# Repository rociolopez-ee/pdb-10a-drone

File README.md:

# 🔋 Drone Power Distribution Board

A 2-layer power distribution PCB designed for lightweight drones. Capable of distributing up to **10A of current**, this board is optimized for compact layouts and robust power handling.

## 📐 Board Specifications

- **Layers**: 2  
- **Board Size**: 2.0924 x 3.4843 in (5.31 x 8.85 cm)  
- **Max Current**: 10A  
- **Application**: Power regulation and distribution for quadcopters or fixed-wing drones  
- **Copper Weight**: 2 oz  
- **Input Voltage Range**: 7V–25V (3S–6S LiPo)

## 🛠️ Features

- Input via XT60 or direct-solder pads
- Multiple output rails (ESCs, accessories, BEC)
- Wide ground and V+ copper pours for high current
- Mounting holes for vibration-isolated installation
- Compatible with common LiPo packs and drone frames

## 📁 Repository Contents

- `/schematics/` – Schematic files (.kicad_sch)
- `/pcb_layout/` – PCB layout files (.kicad_pcb) + Gerbers
- `/BOM/` – Bill of Materials (CSV or Excel)
- `/images/` – Board renderings and layout previews

## 🖼️ Preview

## 👩‍💻 Designed by

[Rocio Lopez](https://github.com/rociolopez)

---

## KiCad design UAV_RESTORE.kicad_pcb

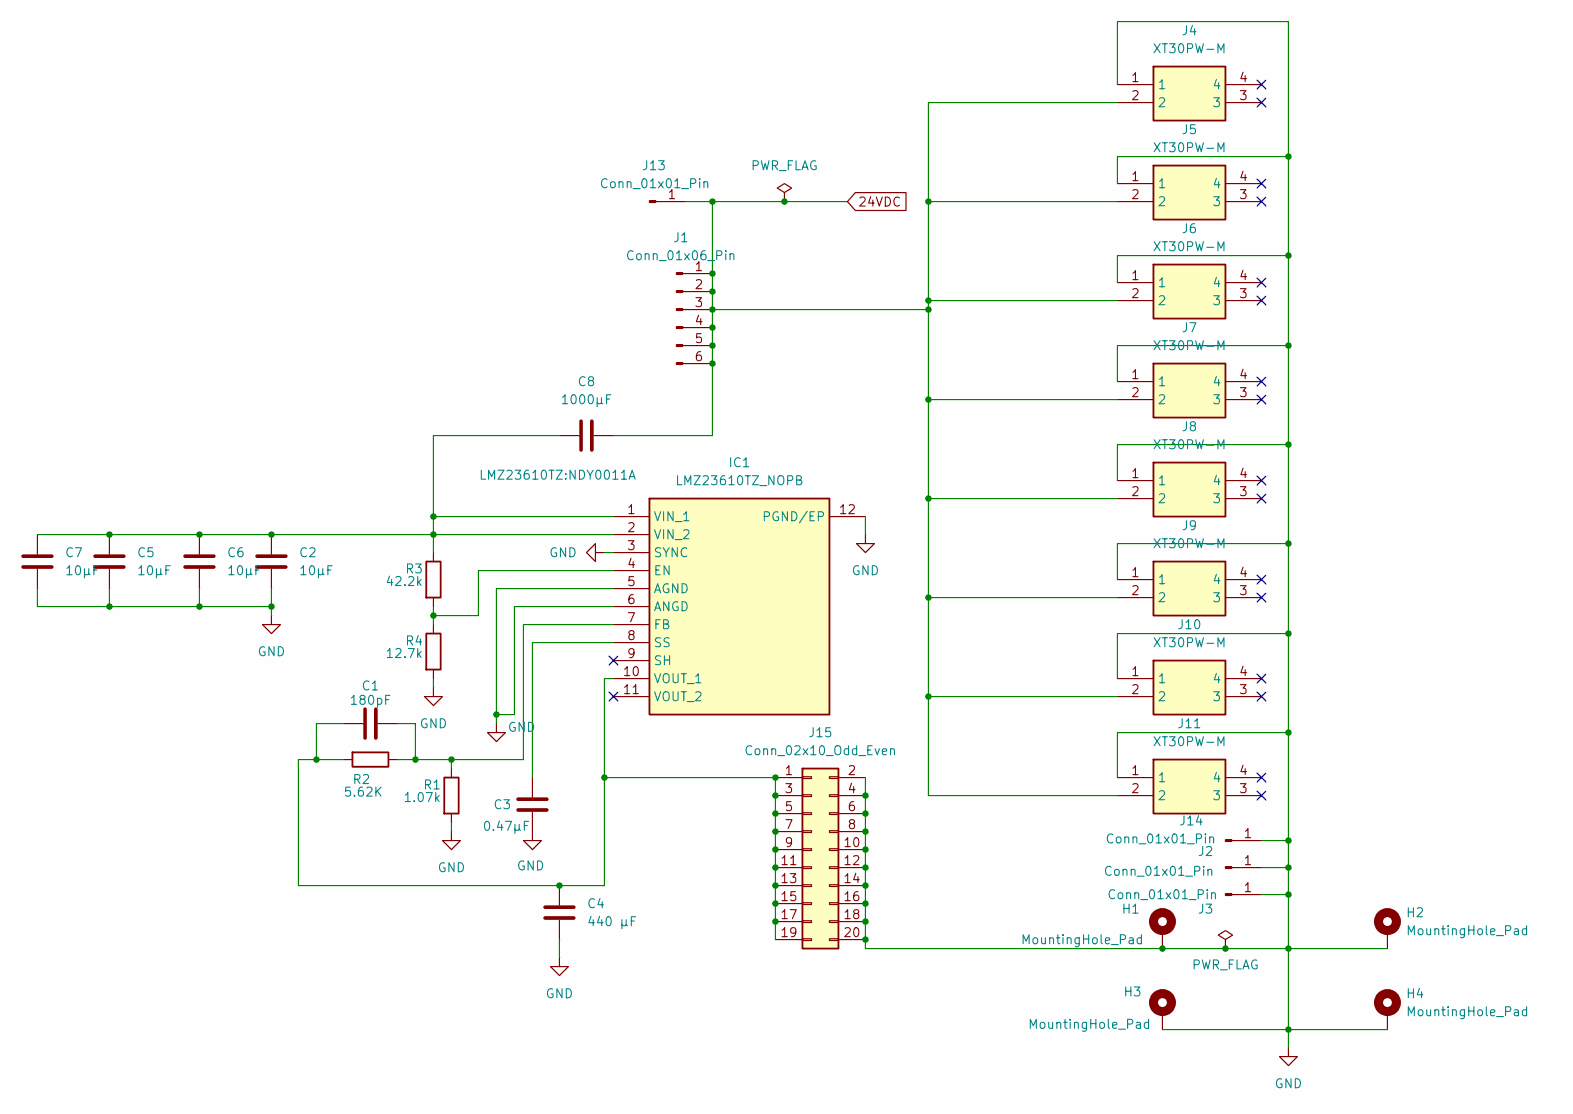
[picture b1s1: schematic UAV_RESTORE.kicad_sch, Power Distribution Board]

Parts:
C1: 180pF; C_1206_3216Metric
C2, C5, C6, C7: 10µF; C_1206_3216Metric
C3: 0.47µF; C_1206_3216Metric
C4: 440 µF; CP_Radial_D10.0mm_P5.00mm
C8: 1000µF; CP_Radial_D12.5mm_P5.00mm
H1, H2, H3, H4: MountingHole_Pad; MountingHole_3mm_Pad
IC1: LMZ23610TZ_NOPB; NDY0011A; Mouser Part Number 926-LMZ23610TZ/NOPB
J1: Conn_01x06_Pin; PinHeader_1x06_P2.54mm_Vertical
J2, J3: Conn_01x01_Pin; PinHeader_1x01_P2.54mm_Vertical
J4, J5, J6, J7, J8, J9, J10, J11: XT30PW-M; AMASS_XT30PW-F_1x02_P2.50mm_Horizontal; Manufacturer_Part_Number XT30PW-M
J13, J14: Conn_01x01_Pin; SolderWire-1.5sqmm_1x01_D1.7mm_OD3.9mm
J15: Conn_02x10_Odd_Even; PinHeader_2x10_P2.00mm_Vertical
R1: 1.07k; R_1206_3216Metric
R2: 5.62K; R_1206_3216Metric
R3: 42.2k; R_1206_3216Metric
R4: 12.7k; R_1206_3216Metric

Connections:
24VDC: C8.1, J1.1, J1.2, J1.3, J1.4, J1.5, J1.6, J4.2, J5.2, J6.2, J7.2, J8.2, J9.2, J10.2, J11.2, J13.1
GND: C2.2, C3.2, C4.2, C5.2, C6.2, C7.2, H1.1, H2.1, H3.1, H4.1, IC1.3 (SYNC), IC1.5 (AGND), IC1.6 (ANGD), IC1.12 (PGND/EP), J2.1, J3.1, J4.1, J5.1, J6.1, J7.1, J8.1, J9.1, J10.1, J11.1, J14.1, J15.2, J15.4, J15.6, J15.8, J15.10, J15.12, J15.14, J15.16, J15.18, J15.20, R1.2, R4.2
unnamed: IC1.4 (EN), R3.2, R4.1
unnamed: C1.2, IC1.7 (FB), R1.1, R2.1
unnamed: C3.1, IC1.8 (SS)
unnamed: C2.1, C5.1, C6.1, C7.1, C8.2, IC1.1 (VIN_1), IC1.2 (VIN_2), R3.1
unnamed: C1.1, C4.1, IC1.10 (VOUT_1), J15.1, J15.3, J15.5, J15.7, J15.9, J15.11, J15.13, J15.15, J15.17, J15.19, R2.2

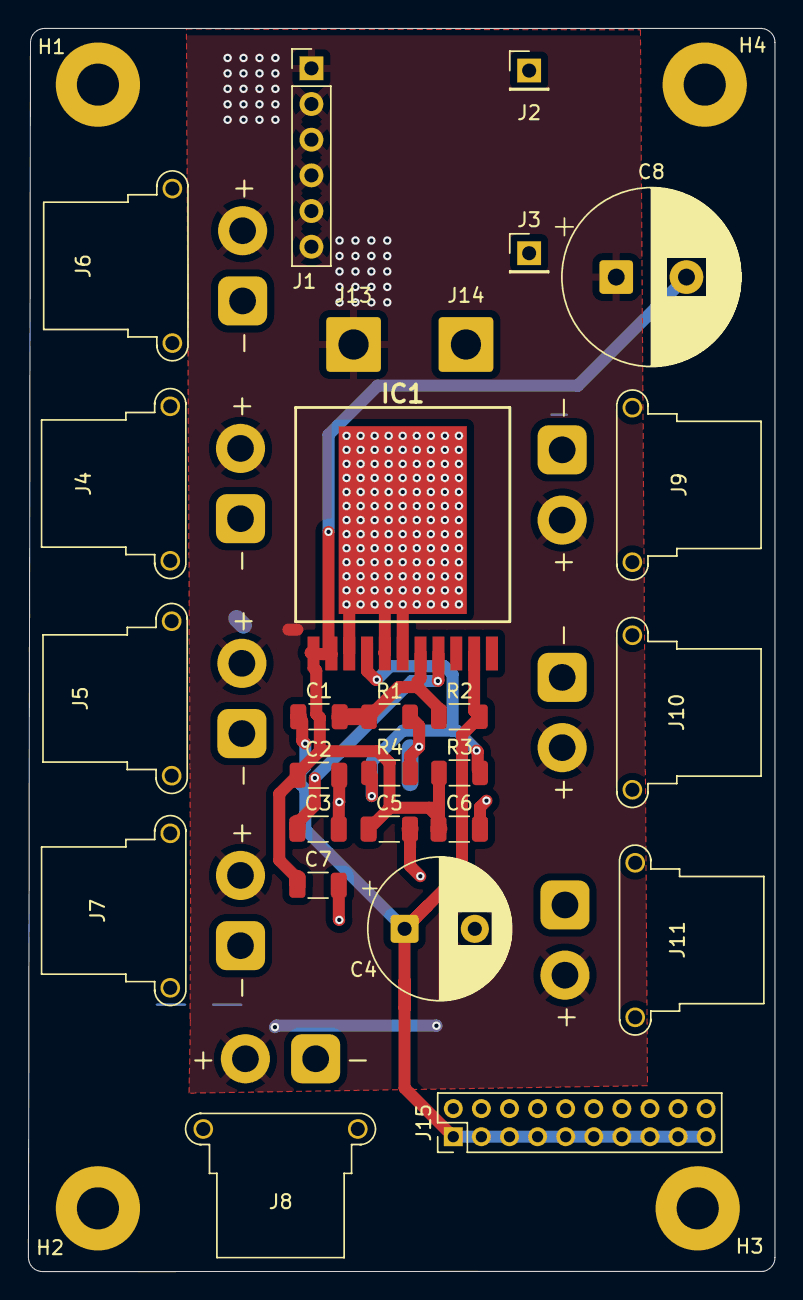
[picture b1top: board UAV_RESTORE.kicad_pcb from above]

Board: 2 copper layers, 53.1 x 88.5 mm, 31 parts (0 on the bottom side), 7 nets.

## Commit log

2025-08-19 Create images
2025-08-19 Update README.md
    added PCB image
